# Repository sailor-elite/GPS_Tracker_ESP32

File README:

# ESP 32 GPS Tracker with TTL Signal Isolation  

Main purpose of this project is to create Redundant NMEA Distribution System using ESP 32, RS 422 to TTL converter and TTL Signal Isolation board. 

# Components

- 6x ESP32 S3 N16R8 DevKitC-1 16MB Flash 8MB PSRAM 2 x USB C
- 2x GPS GY-NEO6MV2 NEO-6M 
- 4x LCD TFT 2.4 " Touch Display

# General Schematic of the system

#PCB Layout of TTL Signal Isolation board

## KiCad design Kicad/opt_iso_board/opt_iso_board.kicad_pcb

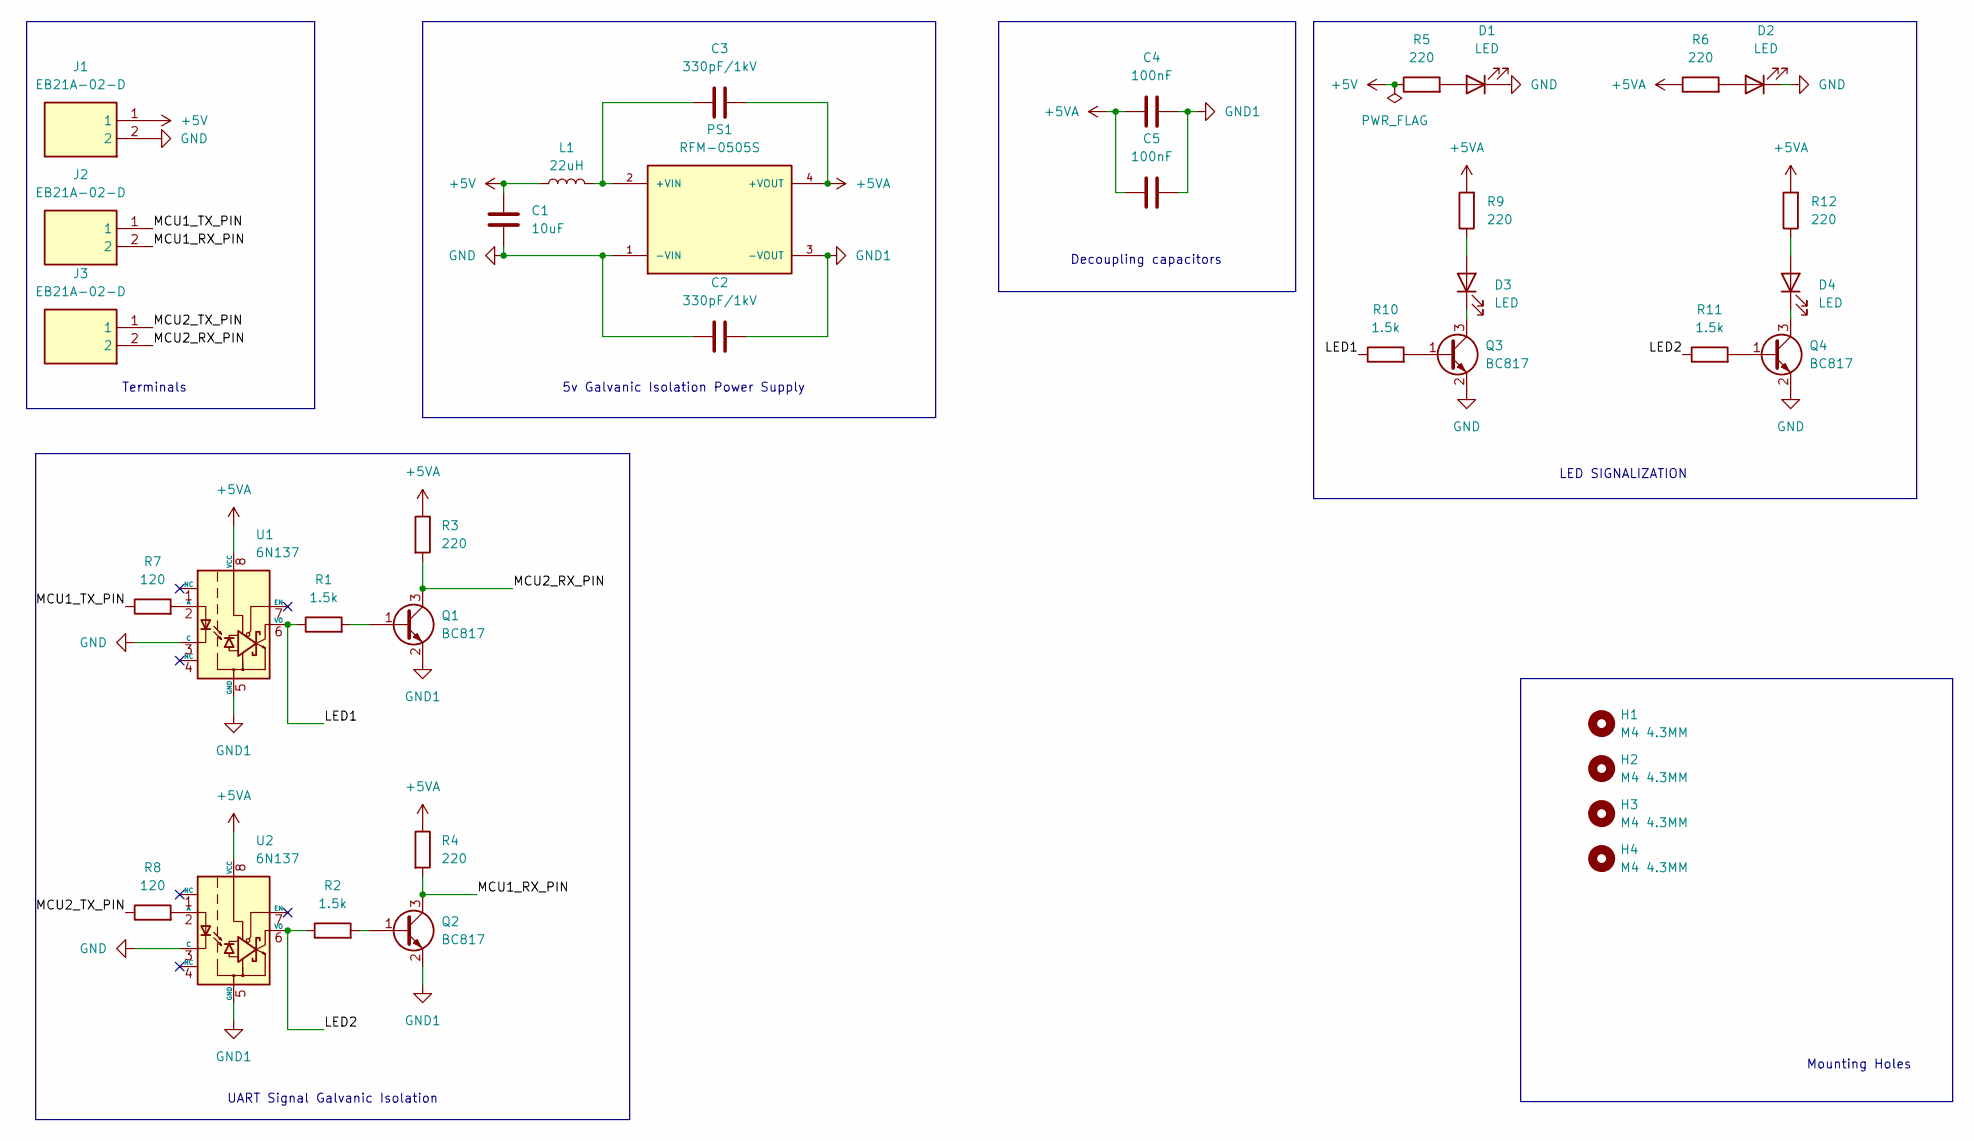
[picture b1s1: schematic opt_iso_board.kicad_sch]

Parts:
C1: 10uF; C_1210_3225Metric
C2, C3: 330pF/1kV; C_1210_3225Metric
C4, C5: 100nF; C_1210_3225Metric
D1, D2, D3, D4: LED; LED_D2.0mm_W4.8mm_H2.5mm_FlatTop
H1, H2, H3, H4: M4 4.3MM; MountingHole_4.3mm_M4
J1, J2, J3: EB21A-02-D; EB21A02D; Manufacturer_Part_Number EB21A-02-D
L1: 22uH; L_1210_3225Metric
PS1: RFM-0505S; CONV_RFM-0505S; PARTREV 0
Q1, Q2, Q3, Q4: BC817; SOT-23
R1, R2, R10, R11: 1.5k; R_1210_3225Metric
R3, R4, R5, R6, R9, R12: 220; R_1210_3225Metric
R7, R8: 120; R_1210_3225Metric
U1, U2: 6N137; DIP-8_W7.62mm

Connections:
+5V: C1.1, J1.1, L1.1, R5.1
+5VA: C3.1, C4.2, C5.2, PS1.4 (+VOUT), R3.1, R4.1, R6.1, R9.2, R12.2, U1.8 (VCC), U2.8 (VCC)
/LED1: R1.1, R10.1, U1.6 (VO)
/LED2: R2.1, R11.1, U2.6 (VO)
/MCU1_RX_PIN: J2.2, Q2.3 (C), R4.2
/MCU1_TX_PIN: J2.1, R7.1
/MCU2_RX_PIN: J3.2, Q1.3 (C), R3.2
/MCU2_TX_PIN: J3.1, R8.1
GND: C1.2, C2.2, D1.1 (K), D2.1 (K), J1.2, PS1.1 (-VIN), Q3.2 (E), Q4.2 (E), U1.3 (C), U2.3 (C)
GND1: C2.1, C4.1, C5.1, PS1.3 (-VOUT), Q1.2 (E), Q2.2 (E), U1.5 (GND), U2.5 (GND)
unnamed: D1.2 (A), R5.2
unnamed: D2.2 (A), R6.2
unnamed: D3.2 (A), R9.1
unnamed: D3.1 (K), Q3.3 (C)
unnamed: D4.2 (A), R12.1
unnamed: D4.1 (K), Q4.3 (C)
unnamed: C3.2, L1.2, PS1.2 (+VIN)
unnamed: Q1.1 (B), R1.2
unnamed: Q2.1 (B), R2.2
unnamed: Q3.1 (B), R10.2
unnamed: Q4.1 (B), R11.2
unnamed: R7.2, U1.2 (A)
unnamed: R8.2, U2.2 (A)

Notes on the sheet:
UART Signal Galvanic Isolation
LED SIGNALIZATION
Decoupling capacitors
5v Galvanic Isolation Power Supply
Terminals
Mounting Holes

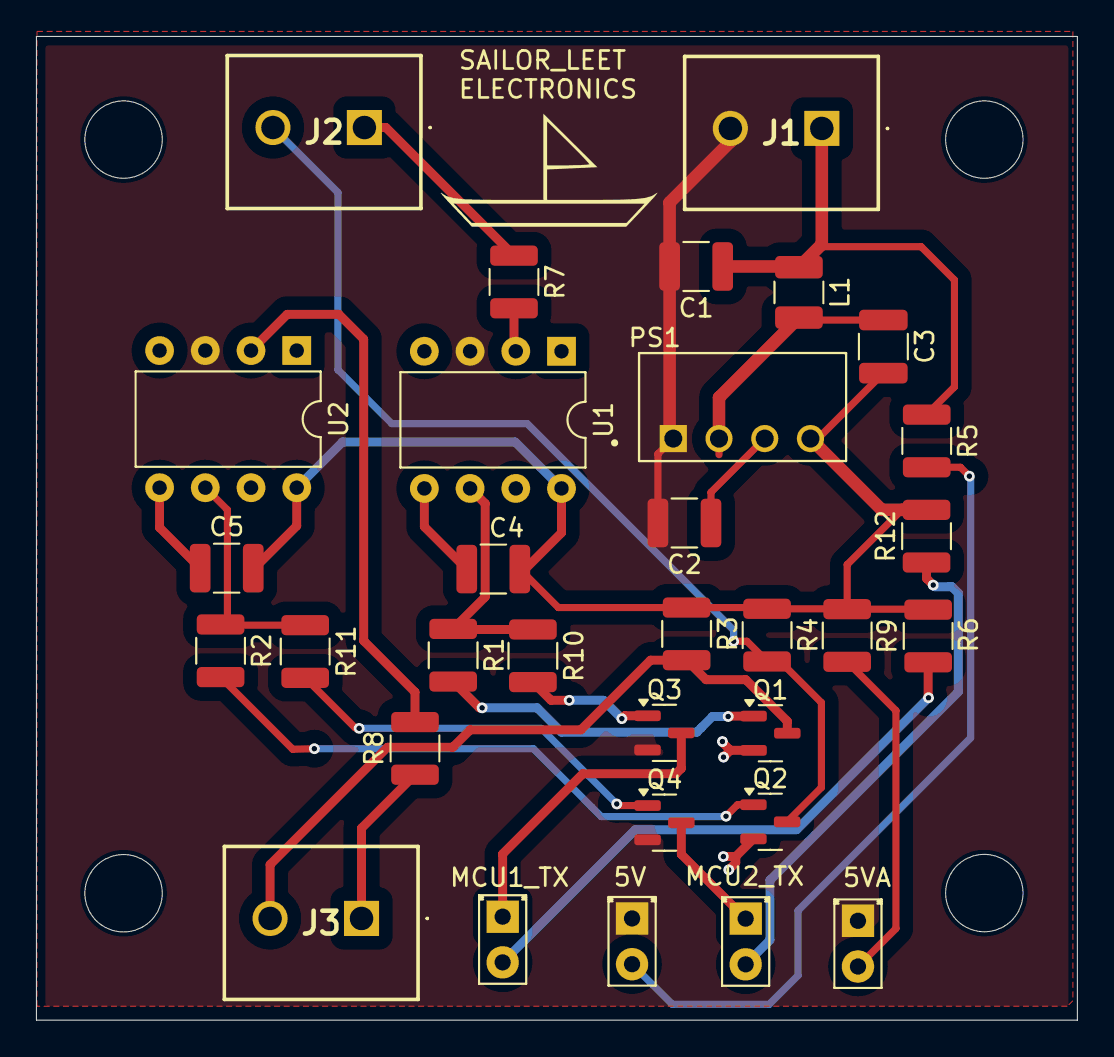
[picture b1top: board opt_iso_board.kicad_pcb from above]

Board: 2 copper layers, 57.8 x 54.6 mm, 36 parts (0 on the bottom side), 23 nets.

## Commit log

2024-09-10 Creating new repository
2024-09-10 Block diagram presenting desired system
2024-10-07 PCB design for UART Signal isolation
2024-10-07 3D Visualization of PCB
2024-10-07 just another README to README.MD rename
